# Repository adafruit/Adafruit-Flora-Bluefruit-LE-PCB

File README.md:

## Adafruit Flora Bluefruit LE PCB
<a href="http://www.adafruit.com/products/2487"><br/>
Click here to purchase one from the Adafruit shop</a>

Would you like to add powerful and easy-to-use Bluetooth Low Energy to your wearable FLORA project? Heck yeah! With BLE now included in modern smart phones and tablets, its fun to add wireless connectivity. So what you really need is the new Adafruit Flora Bluefruit LE!

The Flora Bluefruit LE makes it easy to add Bluetooth Low Energy connectivity to your Flora. Sew 4 traces (or solder 4 wires) and BooM! Bluetooth Low Energy!

Get started fast with the Bluefruit App!

Using our Bluefruit iOS App or Android App, you can quickly get your interactive project prototyped by using your iOS or Android phone/tablet as a controller. We have a color picker, quaternion/accelerometer/gyro/magnetometer or location (GPS), and an 8-button control game pad. After you connect to the Bluefruit, you can send commands wirelessly in under 10 minutes

PCB files for the Adafruit Bluefruit LE PCB. The format is EagleCAD schematic and board layout
- https://www.adafruit.com/product/2487

### License

Adafruit invests time and resources providing this open source design, please support Adafruit and open-source hardware by purchasing products from [Adafruit](https://www.adafruit.com)!

All text above must be included in any redistribution

Designed by Limor Fried/Ladyada for Adafruit Industries.
Creative Commons Attribution/Share-Alike, all text above must be included in any redistribution. 
See license.txt for additional information.

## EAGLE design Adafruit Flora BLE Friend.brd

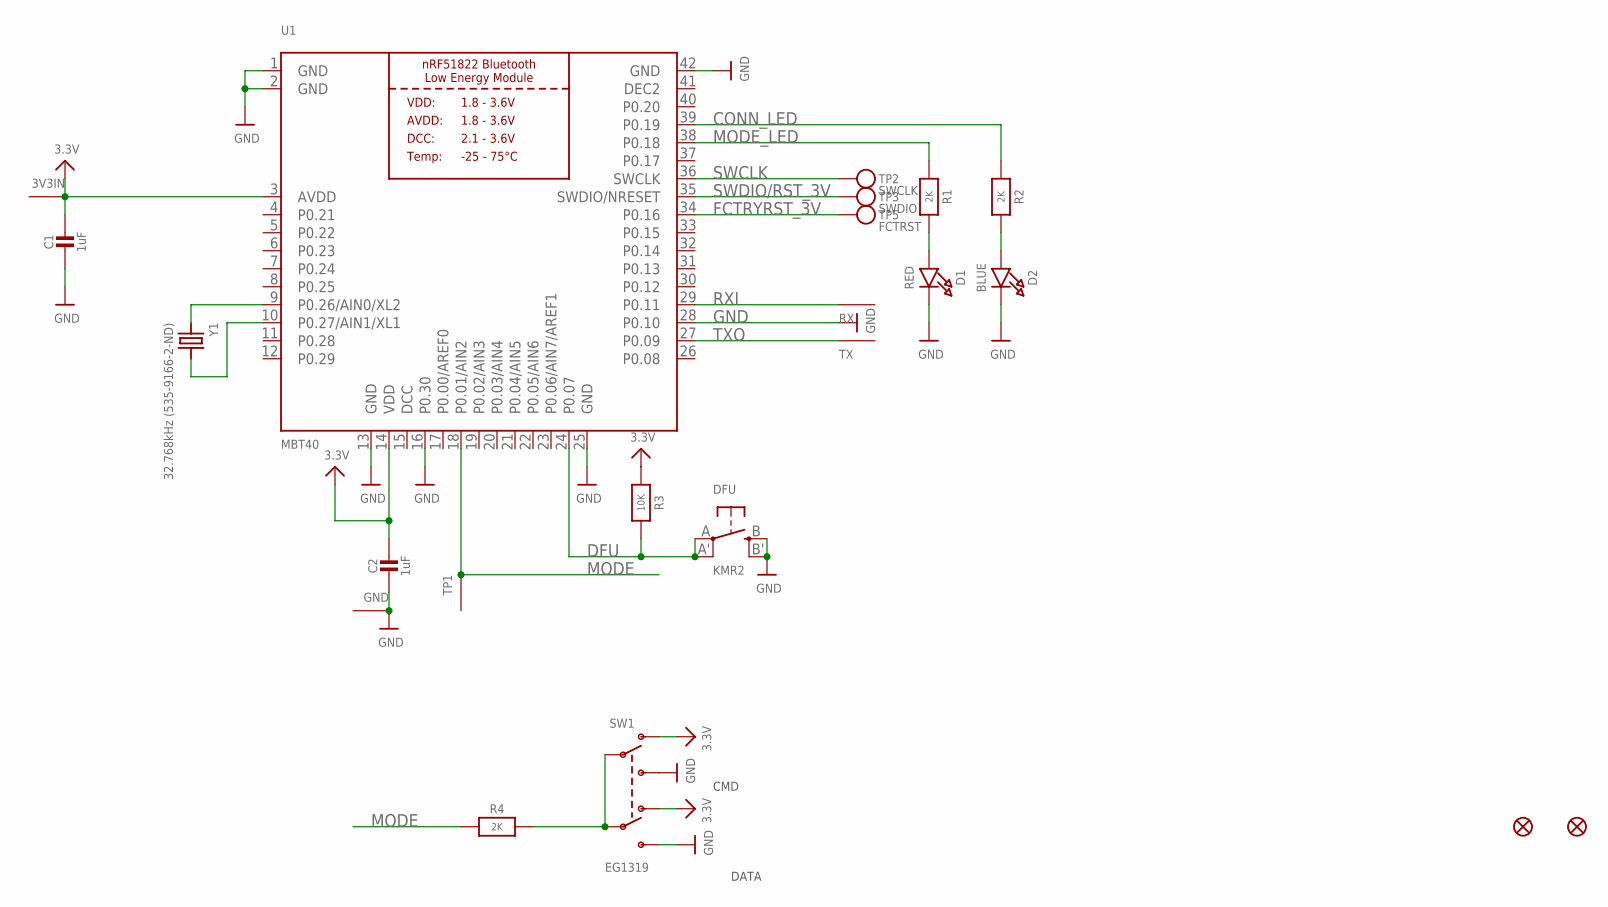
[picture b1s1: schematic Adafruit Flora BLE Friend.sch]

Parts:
3V3IN: SEWTAP-2.0IN; SEWINGTAP_2.0
C1, C2: 1uF; 0805-NO
D1: RED; CHIPLED_0805_NOOUTLINE
D2: BLUE; CHIPLED_0805_NOOUTLINE
DFU: KMR2; BTN_KMR2_4.6X2.8
FID1, FID2: FIDUCIAL""; FIDUCIAL_1MM
GND: SEWTAP-2.0IN; SEWINGTAP_2.0
R1, R2, R4: 2K; 0805-NO
R3: 10K; 0805-NO
RX: SEWTAP-2.0IN; SEWINGTAP_2.0
SW1: EG1319; EG1390
TP1: SEWTAP-2.0IN; SEWINGTAP_2.0
TP2: SWCLK; PAD-1.5X2.0
TP3: SWDIO; PAD-1.5X2.0
TP5: FCTRST; PAD-1.5X2.0
TX: SEWTAP-2.0IN; SEWINGTAP_2.0
U1: MBT40; BLE_MODULE_RAYTAC_MDBT40
Y1: 32.768kHz (535-9166-2-ND); CRYSTAL_CYL_2X6MM_SMT

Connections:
3.3V: 3V3IN.P$1, C1.1, C2.1, R3.1, SW1.O1, SW1.O2, U1.3 (AVDD), U1.14 (VDD)
CONN_LED: R2.1, U1.39 (P0.19)
DCC: U1.15 (DCC)
DEC2: U1.41 (DEC2)
DFU: DFU.A, DFU.A' (P1), R3.2, U1.24 (P0.07)
FCTRYRST_3V: TP5.P$1, U1.34 (P0.16)
GND: C1.2, C2.2, D1.C, D2.C, DFU.B (S), DFU.B' (S1), GND.P$1, SW1.S1, SW1.S2, U1.1 (GND), U1.2 (GND), U1.13 (GND), U1.16 (P0.30), U1.25 (GND), U1.28 (P0.10), U1.42 (GND)
MODE: R4.1, TP1.P$1, U1.18 (P0.01/AIN2)
MODE_LED: R1.1, U1.38 (P0.18)
unnamed: R4.2, SW1.P1, SW1.P2
unnamed: D1.A, R1.2
unnamed: D2.A, R2.2
unnamed: U1.9 (P0.26/AIN0/XL2), Y1.1
unnamed: U1.10 (P0.27/AIN1/XL1), Y1.2
RXI: RX.P$1, U1.29 (P0.11)
SWCLK: TP2.P$1, U1.36 (SWCLK)
SWDIO/RST_3V: TP3.P$1, U1.35 (SWDIO/NRESET)
TXO: TX.P$1, U1.27 (P0.09)

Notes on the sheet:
DATA
CMD

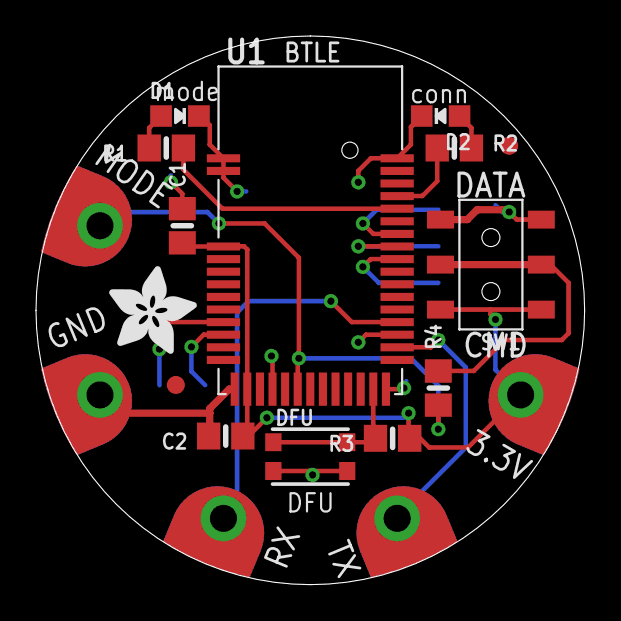
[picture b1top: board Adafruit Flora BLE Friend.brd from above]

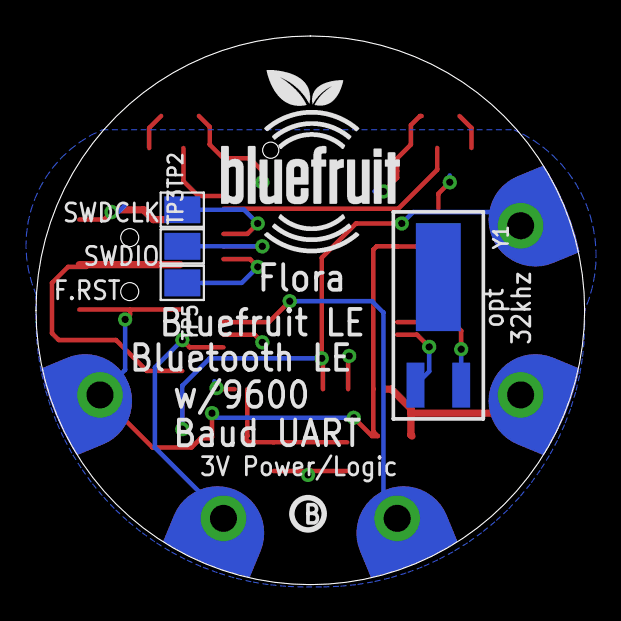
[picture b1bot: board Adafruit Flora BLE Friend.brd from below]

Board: 2 copper layers, 30.5 x 30.5 mm, 26 parts (7 on the bottom side), 16 nets.

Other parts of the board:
U$6: ADAFRUIT_5MM
U$7: FLORASMALL
U$23: BLUEFRUITLOGO_100MM
U$24: PCBFEAT-REV-040

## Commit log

2016-04-03 init
